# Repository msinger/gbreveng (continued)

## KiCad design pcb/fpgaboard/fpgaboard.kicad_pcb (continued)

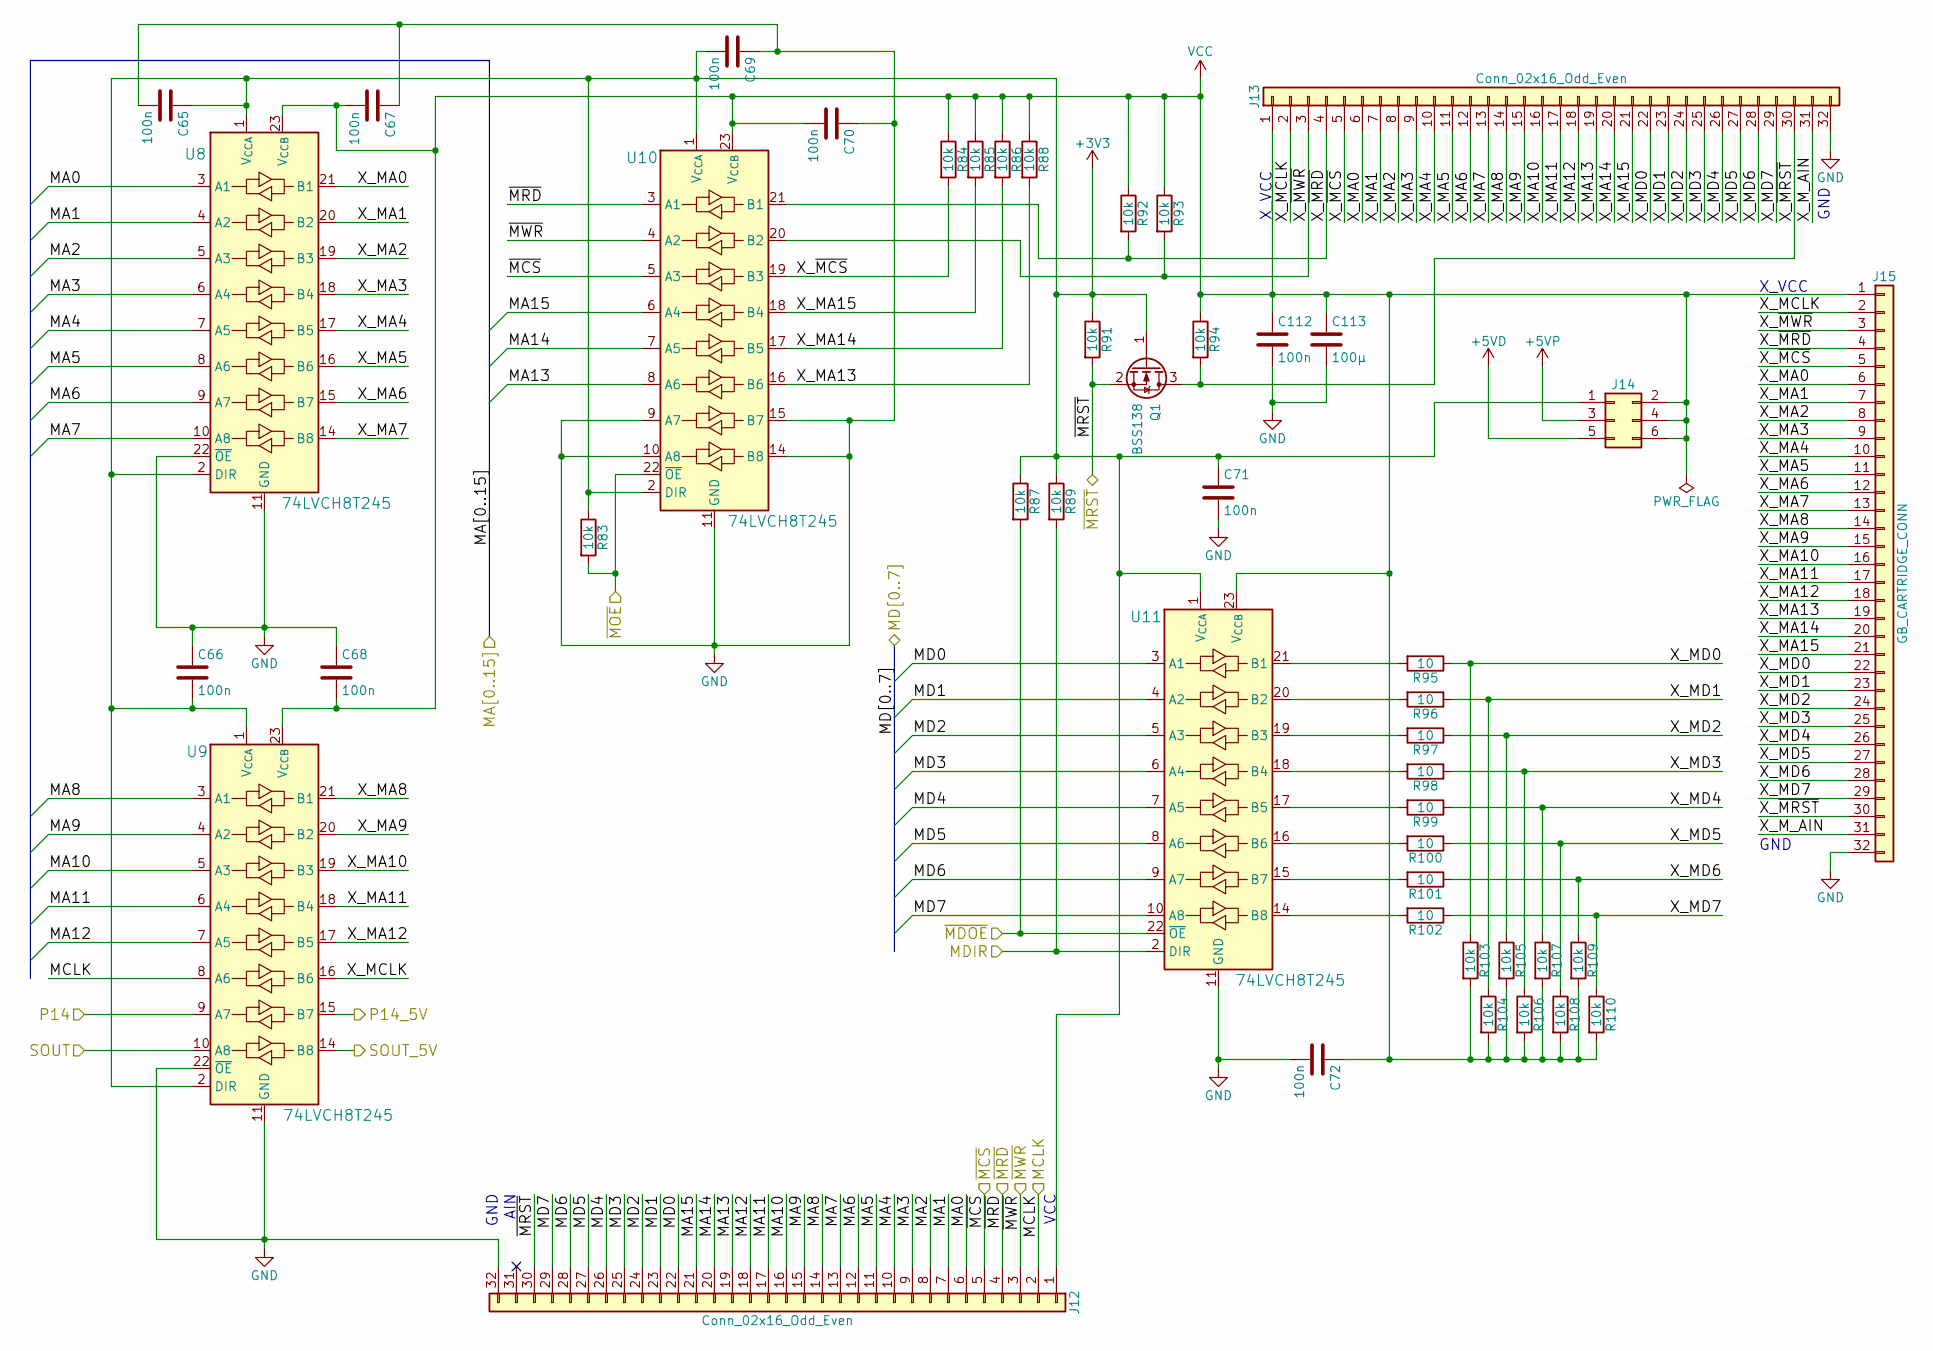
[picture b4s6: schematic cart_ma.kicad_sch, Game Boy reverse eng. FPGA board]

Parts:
C65, C66, C67, C68, C69, C70, C71, C72, C112: 100n; C_0402_1005Metric_Pad0.74x0.62mm_HandSolder
C113: 100µ; C_1206_3216Metric
J12, J13: Conn_02x16_Odd_Even; PinHeader_2x16_P2.54mm_Vertical
J14: Conn_02x03_Odd_Even; PinHeader_2x03_P2.54mm_Vertical
J15: GB_CARTRIDGE_CONN; Cartridge_Socket_SMD
Q1: BSS138; SOT-323_SC-70
R83, R84, R85, R86, R87, R88, R89, R91, R92, R93, R94, R103, R104, R105, R106, R107, R108, R109, R110: 10k; R_0402_1005Metric
R95, R96, R97, R98, R99, R100, R101, R102: 10; R_0603_1608Metric
U8, U9, U10, U11: 74LVCH8T245; TSSOP-24_4.4x7.8mm_P0.65mm

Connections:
+3V3: C65.1, C66.2, C69.2, C71.1, J12.1, J14.1, Q1.1 (G), R83.1, R87.1, R89.1, R91.1, U8.1 (V_{CCA}), U8.2 (DIR), U9.1 (V_{CCA}), U9.2 (DIR), U10.1 (V_{CCA}), U10.2 (DIR), U11.1 (V_{CCA}); also elsewhere on the board
+5VD: J14.5; also elsewhere on the board
+5VP: J14.3; also elsewhere on the board
/Bank0: Display, Keyboard, Clock/P14: U9.9 (A7); also elsewhere on the board
/Bank2: SDCard/CART_MA_CLK: J12.2, U9.8 (A6); also elsewhere on the board
/Bank2: SDCard/CART_MA_DIR: R89.2, U11.2 (DIR); also elsewhere on the board
/Bank2: SDCard/CART_MA_~CS: J12.5, U10.5 (A3); also elsewhere on the board
/Bank2: SDCard/CART_MA_~OE: R83.2, U10.22 (~OE); also elsewhere on the board
/Bank2: SDCard/CART_MA_~OE~_DATA: R87.2, U11.22 (~OE); also elsewhere on the board
/Bank2: SDCard/CART_MA_~RST: J12.30, Q1.2 (S), R91.2; also elsewhere on the board
/Bank2: SDCard/MA0: J12.6, U8.3 (A1); also elsewhere on the board
/Bank2: SDCard/MA1: J12.7, U8.4 (A2); also elsewhere on the board
/Bank2: SDCard/MA2: J12.8, U8.5 (A3); also elsewhere on the board
/Bank2: SDCard/MA3: J12.9, U8.6 (A4); also elsewhere on the board
/Bank2: SDCard/MA4: J12.10, U8.7 (A5); also elsewhere on the board
/Bank2: SDCard/MA5: J12.11, U8.8 (A6); also elsewhere on the board
/Bank2: SDCard/MA6: J12.12, U8.9 (A7); also elsewhere on the board
/Bank2: SDCard/MA7: J12.13, U8.10 (A8); also elsewhere on the board
/Bank2: SDCard/MA8: J12.14, U9.3 (A1); also elsewhere on the board
/Bank2: SDCard/MA9: J12.15, U9.4 (A2); also elsewhere on the board
/Bank2: SDCard/MA10: J12.16, U9.5 (A3); also elsewhere on the board
/Bank2: SDCard/MA11: J12.17, U9.6 (A4); also elsewhere on the board
/Bank2: SDCard/MA12: J12.18, U9.7 (A5); also elsewhere on the board
/Bank2: SDCard/MA13: J12.19, U10.8 (A6); also elsewhere on the board
/Bank2: SDCard/MA14: J12.20, U10.7 (A5); also elsewhere on the board
/Bank2: SDCard/MA15: J12.21, U10.6 (A4); also elsewhere on the board
/Bank2: SDCard/MD0: J12.22, U11.3 (A1); also elsewhere on the board
/Bank2: SDCard/MD1: J12.23, U11.4 (A2); also elsewhere on the board
/Bank2: SDCard/MD2: J12.24, U11.5 (A3); also elsewhere on the board
/Bank2: SDCard/MD3: J12.25, U11.6 (A4); also elsewhere on the board
/Bank2: SDCard/MD4: J12.26, U11.7 (A5); also elsewhere on the board
/Bank2: SDCard/MD5: J12.27, U11.8 (A6); also elsewhere on the board
/Bank2: SDCard/MD6: J12.28, U11.9 (A7); also elsewhere on the board
/Bank2: SDCard/MD7: J12.29, U11.10 (A8); also elsewhere on the board
/Bank3: LEDs, Switches/SOUT: U9.10 (A8); also elsewhere on the board
/Cartridge Master Slot/P14_5V: U9.15 (B7); also elsewhere on the board
/Cartridge Master Slot/SOUT_5V: U9.14 (B8); also elsewhere on the board
/Cartridge Master Slot/X_AIN: J13.31, J15.31
/Cartridge Master Slot/X_MA0: J13.6, J15.6, U8.21 (B1)
/Cartridge Master Slot/X_MA1: J13.7, J15.7, U8.20 (B2)
/Cartridge Master Slot/X_MA2: J13.8, J15.8, U8.19 (B3)
/Cartridge Master Slot/X_MA3: J13.9, J15.9, U8.18 (B4)
/Cartridge Master Slot/X_MA4: J13.10, J15.10, U8.17 (B5)
/Cartridge Master Slot/X_MA5: J13.11, J15.11, U8.16 (B6)
/Cartridge Master Slot/X_MA6: J13.12, J15.12, U8.15 (B7)
/Cartridge Master Slot/X_MA7: J13.13, J15.13, U8.14 (B8)
/Cartridge Master Slot/X_MA8: J13.14, J15.14, U9.21 (B1)
/Cartridge Master Slot/X_MA9: J13.15, J15.15, U9.20 (B2)
/Cartridge Master Slot/X_MA10: J13.16, J15.16, U9.19 (B3)
/Cartridge Master Slot/X_MA11: J13.17, J15.17, U9.18 (B4)
/Cartridge Master Slot/X_MA12: J13.18, J15.18, U9.17 (B5)
/Cartridge Master Slot/X_MA13: J13.19, J15.19, R88.2, U10.16 (B6)
/Cartridge Master Slot/X_MA14: J13.20, J15.20, R86.2, U10.17 (B5)
/Cartridge Master Slot/X_MA15: J13.21, J15.21, R85.2, U10.18 (B4)
/Cartridge Master Slot/X_MCLK: J13.2, J15.2, U9.16 (B6)
/Cartridge Master Slot/X_MD0: J13.22, J15.22, R95.1, R103.1
/Cartridge Master Slot/X_MD1: J13.23, J15.23, R96.1, R104.1
/Cartridge Master Slot/X_MD2: J13.24, J15.24, R97.1, R105.1
/Cartridge Master Slot/X_MD3: J13.25, J15.25, R98.1, R106.1
/Cartridge Master Slot/X_MD4: J13.26, J15.26, R99.1, R107.1
/Cartridge Master Slot/X_MD5: J13.27, J15.27, R100.1, R108.1
/Cartridge Master Slot/X_MD6: J13.28, J15.28, R101.1, R109.1
/Cartridge Master Slot/X_MD7: J13.29, J15.29, R102.1, R110.1
/Cartridge Master Slot/X_~MCS: J13.5, J15.5, R84.2, U10.19 (B3)
/Cartridge Master Slot/X_~MRD: J13.4, J15.4, R92.2, U10.21 (B1)
/Cartridge Master Slot/X_~MRST: J13.30, J15.30, Q1.3 (D), R94.2
/Cartridge Master Slot/X_~MWR: J13.3, J15.3, R93.2, U10.20 (B2)
/~MRD: J12.4, U10.3 (A1); also elsewhere on the board
/~MWR: J12.3, U10.4 (A2); also elsewhere on the board
GND: C65.2, C66.1, C67.2, C68.1, C69.1, C70.1, C71.2, C72.2, C112.2, C113.2, J12.32, J13.32, J15.32, U8.11 (GND), U8.12 (GND), U8.13 (GND), U8.22 (~OE), U9.11 (GND), U9.12 (GND), U9.13 (GND), U9.22 (~OE), U10.9 (A7), U10.10 (A8), U10.11 (GND), U10.12 (GND), U10.13 (GND), U10.14 (B8), U10.15 (B7), U11.11 (GND), U11.12 (GND), U11.13 (GND); also elsewhere on the board
unnamed: R95.2, U11.21 (B1)
unnamed: R96.2, U11.20 (B2)
unnamed: R97.2, U11.19 (B3)
unnamed: R98.2, U11.18 (B4)
unnamed: R99.2, U11.17 (B5)
unnamed: R100.2, U11.16 (B6)
unnamed: R101.2, U11.15 (B7)
unnamed: R102.2, U11.14 (B8)
VCC: C67.1, C68.2, C70.2, C72.1, C112.1, C113.1, J13.1, J14.2, J14.4, J14.6, J15.1, R84.1, R85.1, R86.1, R88.1, R92.1, R93.1, R94.1, R103.2, R104.2, R105.2, R106.2, R107.2, R108.2, R109.2, R110.2, U8.23 (V_{CCB}), U8.24 (V_{CCB}), U9.23 (V_{CCB}), U9.24 (V_{CCB}), U10.23 (V_{CCB}), U10.24 (V_{CCB}), U11.23 (V_{CCB}), U11.24 (V_{CCB}); also elsewhere on the board

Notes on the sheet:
X_VCC
VCC
AIN
GND

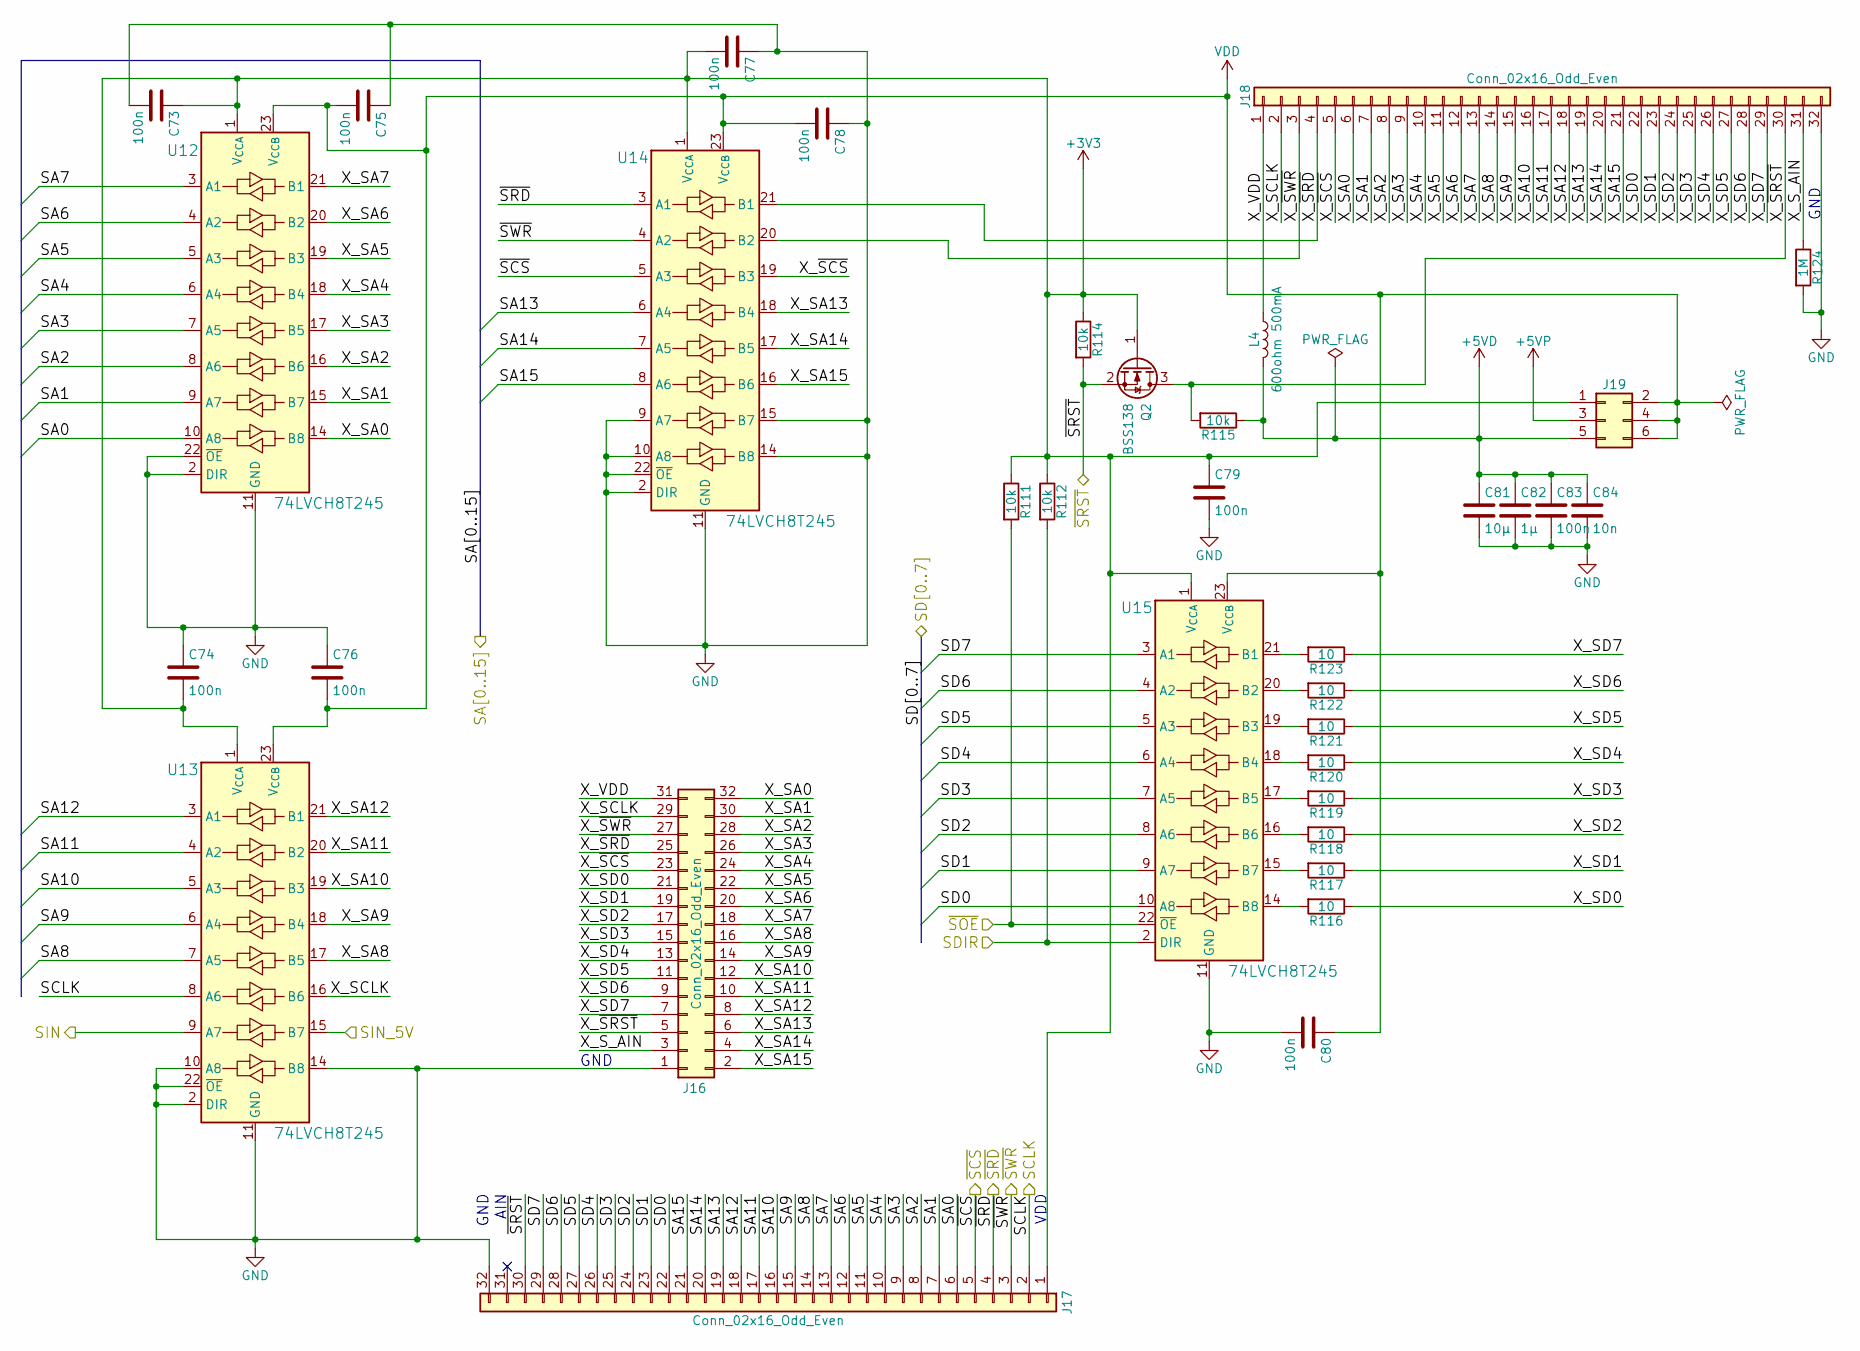
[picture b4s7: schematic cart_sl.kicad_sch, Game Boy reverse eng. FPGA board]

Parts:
C73, C74, C75, C76, C77, C78, C79, C80, C83: 100n; C_0402_1005Metric_Pad0.74x0.62mm_HandSolder
C81: 10µ; C_0603_1608Metric
C82: 1µ; C_0402_1005Metric_Pad0.74x0.62mm_HandSolder
C84: 10n; C_0402_1005Metric_Pad0.74x0.62mm_HandSolder
J16, J17, J18: Conn_02x16_Odd_Even; PinHeader_2x16_P2.54mm_Vertical
J19: Conn_02x03_Odd_Even; PinHeader_2x03_P2.54mm_Vertical
L4: 600ohm 500mA; L_0603_1608Metric
Q2: BSS138; SOT-323_SC-70
R111, R112, R114, R115: 10k; R_0402_1005Metric
R116, R117, R118, R119, R120, R121, R122, R123: 10; R_0603_1608Metric
R124: 1M; R_0402_1005Metric
U12, U13, U14, U15: 74LVCH8T245; TSSOP-24_4.4x7.8mm_P0.65mm

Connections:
+3V3: C73.1, C74.2, C77.2, C79.1, J17.1, J19.1, Q2.1 (G), R111.1, R112.1, R114.1, U12.1 (V_{CCA}), U13.1 (V_{CCA}), U14.1 (V_{CCA}), U15.1 (V_{CCA}); also elsewhere on the board
+5VD: C81.1, C82.1, C83.1, C84.1, J19.5, L4.2, R115.1; also elsewhere on the board
+5VP: J19.3; also elsewhere on the board
/Bank0: Display, Keyboard, Clock/A0: J17.6, U12.10 (A8); also elsewhere on the board
/Bank0: Display, Keyboard, Clock/A1: J17.7, U12.9 (A7); also elsewhere on the board
/Bank0: Display, Keyboard, Clock/A2: J17.8, U12.8 (A6); also elsewhere on the board
/Bank0: Display, Keyboard, Clock/A3: J17.9, U12.7 (A5); also elsewhere on the board
/Bank0: Display, Keyboard, Clock/A4: J17.10, U12.6 (A4); also elsewhere on the board
/Bank0: Display, Keyboard, Clock/A5: J17.11, U12.5 (A3); also elsewhere on the board
/Bank0: Display, Keyboard, Clock/A6: J17.12, U12.4 (A2); also elsewhere on the board
/Bank0: Display, Keyboard, Clock/A7: J17.13, U12.3 (A1); also elsewhere on the board
/Bank0: Display, Keyboard, Clock/A8: J17.14, U13.7 (A5); also elsewhere on the board
/Bank0: Display, Keyboard, Clock/A9: J17.15, U13.6 (A4); also elsewhere on the board
/Bank0: Display, Keyboard, Clock/A10: J17.16, U13.5 (A3); also elsewhere on the board
/Bank0: Display, Keyboard, Clock/A11: J17.17, U13.4 (A2); also elsewhere on the board
/Bank0: Display, Keyboard, Clock/A12: J17.18, U13.3 (A1); also elsewhere on the board
/Bank0: Display, Keyboard, Clock/A13: J17.19, U14.6 (A4); also elsewhere on the board
/Bank0: Display, Keyboard, Clock/A14: J17.20, U14.7 (A5); also elsewhere on the board
/Bank0: Display, Keyboard, Clock/A15: J17.21, U14.8 (A6); also elsewhere on the board
/Bank0: Display, Keyboard, Clock/CART_SL_CLK: J17.2, U13.8 (A6); also elsewhere on the board
/Bank0: Display, Keyboard, Clock/CART_SL_~RD: J17.4, U14.3 (A1); also elsewhere on the board
/Bank0: Display, Keyboard, Clock/CART_SL_~WR: J17.3, U14.4 (A2); also elsewhere on the board
/Bank1: GPIOA/CART_SL_DIR: R112.2, U15.2 (DIR); also elsewhere on the board
/Bank1: GPIOA/CART_SL_~CS: J17.5, U14.5 (A3); also elsewhere on the board
/Bank1: GPIOA/CART_SL_~OE: R111.2, U15.22 (~OE); also elsewhere on the board
/Bank1: GPIOA/CART_SL_~RST: J17.30, Q2.2 (S), R114.2; also elsewhere on the board
/Bank1: GPIOA/D0: J17.22, U15.10 (A8); also elsewhere on the board
/Bank1: GPIOA/D1: J17.23, U15.9 (A7); also elsewhere on the board
/Bank1: GPIOA/D2: J17.24, U15.8 (A6); also elsewhere on the board
/Bank1: GPIOA/D3: J17.25, U15.7 (A5); also elsewhere on the board
/Bank1: GPIOA/D4: J17.26, U15.6 (A4); also elsewhere on the board
/Bank1: GPIOA/D5: J17.27, U15.5 (A3); also elsewhere on the board
/Bank1: GPIOA/D6: J17.28, U15.4 (A2); also elsewhere on the board
/Bank1: GPIOA/D7: J17.29, U15.3 (A1); also elsewhere on the board
/Cartridge Slave Slot/X_A0: J16.32, J18.6, U12.14 (B8)
/Cartridge Slave Slot/X_A1: J16.30, J18.7, U12.15 (B7)
/Cartridge Slave Slot/X_A2: J16.28, J18.8, U12.16 (B6)
/Cartridge Slave Slot/X_A3: J16.26, J18.9, U12.17 (B5)
/Cartridge Slave Slot/X_A4: J16.24, J18.10, U12.18 (B4)
/Cartridge Slave Slot/X_A5: J16.22, J18.11, U12.19 (B3)
/Cartridge Slave Slot/X_A6: J16.20, J18.12, U12.20 (B2)
/Cartridge Slave Slot/X_A7: J16.18, J18.13, U12.21 (B1)
/Cartridge Slave Slot/X_A8: J16.16, J18.14, U13.17 (B5)
/Cartridge Slave Slot/X_A9: J16.14, J18.15, U13.18 (B4)
/Cartridge Slave Slot/X_A10: J16.12, J18.16, U13.19 (B3)
/Cartridge Slave Slot/X_A11: J16.10, J18.17, U13.20 (B2)
/Cartridge Slave Slot/X_A12: J16.8, J18.18, U13.21 (B1)
/Cartridge Slave Slot/X_A13: J16.6, J18.19, U14.18 (B4)
/Cartridge Slave Slot/X_A14: J16.4, J18.20, U14.17 (B5)
/Cartridge Slave Slot/X_A15: J16.2, J18.21, U14.16 (B6)
/Cartridge Slave Slot/X_AIN: J16.3, J18.31, R124.1
/Cartridge Slave Slot/X_CLK: J16.29, J18.2, U13.16 (B6)
/Cartridge Slave Slot/X_D0: J16.21, J18.22, R116.1
/Cartridge Slave Slot/X_D1: J16.19, J18.23, R117.1
/Cartridge Slave Slot/X_D2: J16.17, J18.24, R118.1
/Cartridge Slave Slot/X_D3: J16.15, J18.25, R119.1
/Cartridge Slave Slot/X_D4: J16.13, J18.26, R120.1
/Cartridge Slave Slot/X_D5: J16.11, J18.27, R121.1
/Cartridge Slave Slot/X_D6: J16.9, J18.28, R122.1
/Cartridge Slave Slot/X_D7: J16.7, J18.29, R123.1
/Cartridge Slave Slot/X_VDD: J16.31, J18.1, L4.1
/Cartridge Slave Slot/X_~CS: J16.23, J18.5, U14.19 (B3)
/Cartridge Slave Slot/X_~RD: J16.25, J18.4, U14.21 (B1)
/Cartridge Slave Slot/X_~RST: J16.5, J18.30, Q2.3 (D), R115.2
/Cartridge Slave Slot/X_~WR: J16.27, J18.3, U14.20 (B2)
/SIN: U13.9 (A7); also elsewhere on the board
/SIN_5V: U13.15 (B7); also elsewhere on the board
GND: C73.2, C74.1, C75.2, C76.1, C77.1, C78.1, C79.2, C80.2, C81.2, C82.2, C83.2, C84.2, J16.1, J17.32, J18.32, R124.2, U12.2 (DIR), U12.11 (GND), U12.12 (GND), U12.13 (GND), U12.22 (~OE), U13.2 (DIR), U13.10 (A8), U13.11 (GND), U13.12 (GND), U13.13 (GND), U13.14 (B8), U13.22 (~OE), U14.2 (DIR), U14.9 (A7), U14.10 (A8), U14.11 (GND), U14.12 (GND), U14.13 (GND), U14.14 (B8), U14.15 (B7), U14.22 (~OE), U15.11 (GND), U15.12 (GND), U15.13 (GND); also elsewhere on the board
unnamed: R116.2, U15.14 (B8)
unnamed: R117.2, U15.15 (B7)
unnamed: R118.2, U15.16 (B6)
unnamed: R119.2, U15.17 (B5)
unnamed: R120.2, U15.18 (B4)
unnamed: R121.2, U15.19 (B3)
unnamed: R122.2, U15.20 (B2)
unnamed: R123.2, U15.21 (B1)
VDD: C75.1, C76.2, C78.2, C80.1, J19.2, J19.4, J19.6, U12.23 (V_{CCB}), U12.24 (V_{CCB}), U13.23 (V_{CCB}), U13.24 (V_{CCB}), U14.23 (V_{CCB}), U14.24 (V_{CCB}), U15.23 (V_{CCB}), U15.24 (V_{CCB}); also elsewhere on the board

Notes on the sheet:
GND
AIN
VDD

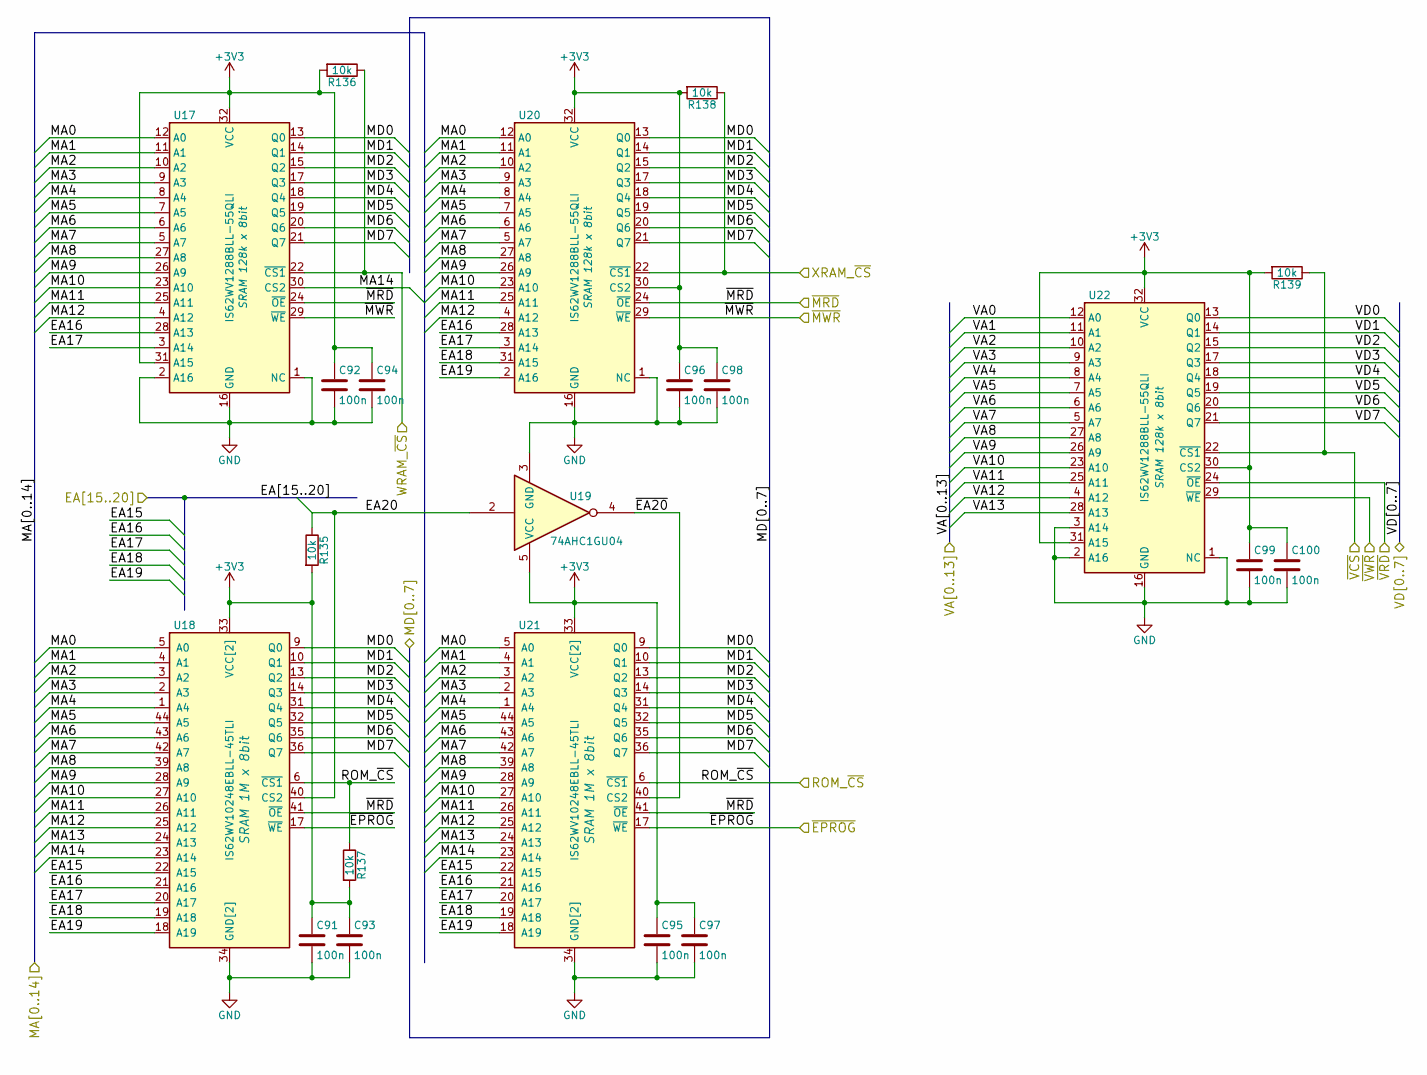
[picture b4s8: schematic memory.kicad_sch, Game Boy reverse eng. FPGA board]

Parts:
C91, C92, C93, C94, C95, C96, C97, C98, C99, C100: 100n; C_0402_1005Metric_Pad0.74x0.62mm_HandSolder
R135, R136, R137, R138, R139: 10k; R_0402_1005Metric
U17, U20, U22: IS62WV1288BLL-55QLI; SSOP-32_11.305x20.495mm_P1.27mm
U18, U21: IS62WV10248EBLL-45TLI; TSOP-II-44_10.16x18.41mm_P0.8mm
U19: 74AHC1GU04; SOT-353_SC-70-5

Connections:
+3V3: C91.1, C92.1, C93.1, C94.1, C95.1, C96.1, C97.1, C98.1, C99.1, C100.1, R135.2, R136.2, R137.2, R138.2, R139.2, U17.31 (A15), U17.32 (VCC), U18.11 (VCC[2]), U18.33 (VCC[2]), U19.5 (VCC), U20.30 (CS2), U20.32 (VCC), U21.11 (VCC[2]), U21.33 (VCC[2]), U22.30 (CS2), U22.31 (A15), U22.32 (VCC); also elsewhere on the board
/Bank1: GPIOA/VA0: U22.12 (A0); also elsewhere on the board
/Bank1: GPIOA/VA1: U22.11 (A1); also elsewhere on the board
/Bank1: GPIOA/VA2: U22.10 (A2); also elsewhere on the board
/Bank1: GPIOA/VA3: U22.9 (A3); also elsewhere on the board
/Bank1: GPIOA/VA4: U22.8 (A4); also elsewhere on the board
/Bank1: GPIOA/VA5: U22.7 (A5); also elsewhere on the board
/Bank1: GPIOA/VA6: U22.6 (A6); also elsewhere on the board
/Bank1: GPIOA/VA7: U22.5 (A7); also elsewhere on the board
/Bank1: GPIOA/VA8: U22.27 (A8); also elsewhere on the board
/Bank1: GPIOA/VA9: U22.26 (A9); also elsewhere on the board
/Bank1: GPIOA/VA10: U22.23 (A10); also elsewhere on the board
/Bank1: GPIOA/VA11: U22.25 (A11); also elsewhere on the board
/Bank1: GPIOA/VA12: U22.4 (A12); also elsewhere on the board
/Bank1: GPIOA/VA13: U22.28 (A13); also elsewhere on the board
/Bank1: GPIOA/VD0: U22.13 (Q0); also elsewhere on the board
/Bank1: GPIOA/VD1: U22.14 (Q1); also elsewhere on the board
/Bank1: GPIOA/VD2: U22.15 (Q2); also elsewhere on the board
/Bank1: GPIOA/VD3: U22.17 (Q3); also elsewhere on the board
/Bank1: GPIOA/VD4: U22.18 (Q4); also elsewhere on the board
/Bank1: GPIOA/VD5: U22.19 (Q5); also elsewhere on the board
/Bank1: GPIOA/VD6: U22.20 (Q6); also elsewhere on the board
/Bank1: GPIOA/VD7: U22.21 (Q7); also elsewhere on the board
/Bank2: SDCard/EA15: U18.22 (A15), U21.22 (A15); also elsewhere on the board
/Bank2: SDCard/EA16: U17.28 (A13), U18.21 (A16), U20.28 (A13), U21.21 (A16); also elsewhere on the board
/Bank2: SDCard/EA17: U17.3 (A14), U18.20 (A17), U20.3 (A14), U21.20 (A17); also elsewhere on the board
/Bank2: SDCard/EA18: U18.19 (A18), U20.31 (A15), U21.19 (A18); also elsewhere on the board
/Bank2: SDCard/EA19: U18.18 (A19), U20.2 (A16), U21.18 (A19); also elsewhere on the board
/Bank2: SDCard/EA20: R135.1, U18.40 (CS2), U19.2; also elsewhere on the board
/Bank2: SDCard/MA0: U17.12 (A0), U18.5 (A0), U20.12 (A0), U21.5 (A0); also elsewhere on the board
/Bank2: SDCard/MA1: U17.11 (A1), U18.4 (A1), U20.11 (A1), U21.4 (A1); also elsewhere on the board
/Bank2: SDCard/MA2: U17.10 (A2), U18.3 (A2), U20.10 (A2), U21.3 (A2); also elsewhere on the board
/Bank2: SDCard/MA3: U17.9 (A3), U18.2 (A3), U20.9 (A3), U21.2 (A3); also elsewhere on the board
/Bank2: SDCard/MA4: U17.8 (A4), U18.1 (A4), U20.8 (A4), U21.1 (A4); also elsewhere on the board
/Bank2: SDCard/MA5: U17.7 (A5), U18.44 (A5), U20.7 (A5), U21.44 (A5); also elsewhere on the board
/Bank2: SDCard/MA6: U17.6 (A6), U18.43 (A6), U20.6 (A6), U21.43 (A6); also elsewhere on the board
/Bank2: SDCard/MA7: U17.5 (A7), U18.42 (A7), U20.5 (A7), U21.42 (A7); also elsewhere on the board
/Bank2: SDCard/MA8: U17.27 (A8), U18.39 (A8), U20.27 (A8), U21.39 (A8); also elsewhere on the board
/Bank2: SDCard/MA9: U17.26 (A9), U18.28 (A9), U20.26 (A9), U21.28 (A9); also elsewhere on the board
/Bank2: SDCard/MA10: U17.23 (A10), U18.27 (A10), U20.23 (A10), U21.27 (A10); also elsewhere on the board
/Bank2: SDCard/MA11: U17.25 (A11), U18.26 (A11), U20.25 (A11), U21.26 (A11); also elsewhere on the board
/Bank2: SDCard/MA12: U17.4 (A12), U18.25 (A12), U20.4 (A12), U21.25 (A12); also elsewhere on the board
/Bank2: SDCard/MA13: U18.24 (A13), U21.24 (A13); also elsewhere on the board
/Bank2: SDCard/MA14: U17.30 (CS2), U18.23 (A14), U21.23 (A14); also elsewhere on the board
/Bank2: SDCard/MD0: U17.13 (Q0), U18.9 (Q0), U20.13 (Q0), U21.9 (Q0); also elsewhere on the board
/Bank2: SDCard/MD1: U17.14 (Q1), U18.10 (Q1), U20.14 (Q1), U21.10 (Q1); also elsewhere on the board
/Bank2: SDCard/MD2: U17.15 (Q2), U18.13 (Q2), U20.15 (Q2), U21.13 (Q2); also elsewhere on the board
/Bank2: SDCard/MD3: U17.17 (Q3), U18.14 (Q3), U20.17 (Q3), U21.14 (Q3); also elsewhere on the board
/Bank2: SDCard/MD4: U17.18 (Q4), U18.31 (Q4), U20.18 (Q4), U21.31 (Q4); also elsewhere on the board
/Bank2: SDCard/MD5: U17.19 (Q5), U18.32 (Q5), U20.19 (Q5), U21.32 (Q5); also elsewhere on the board
/Bank2: SDCard/MD6: U17.20 (Q6), U18.35 (Q6), U20.20 (Q6), U21.35 (Q6); also elsewhere on the board
/Bank2: SDCard/MD7: U17.21 (Q7), U18.36 (Q7), U20.21 (Q7), U21.36 (Q7); also elsewhere on the board
/Bank2: SDCard/ONBRD_~PROG: U18.17 (~WE), U21.17 (~WE); also elsewhere on the board
/Bank2: SDCard/ROM_~CS: R137.1, U18.6 (~CS1), U21.6 (~CS1); also elsewhere on the board
/Bank2: SDCard/WRAM_~CS: R136.1, U17.22 (~CS1); also elsewhere on the board
/Bank2: SDCard/XRAM_~CS: R138.1, U20.22 (~CS1); also elsewhere on the board
/Memory/~MA20: U19.4, U21.40 (CS2)
/~MRD: U17.24 (~OE), U18.41 (~OE), U20.24 (~OE), U21.41 (~OE); also elsewhere on the board
/~MWR: U17.29 (~WE), U20.29 (~WE); also elsewhere on the board
/~VCS: R139.1, U22.22 (~CS1); also elsewhere on the board
/~VRD: U22.24 (~OE); also elsewhere on the board
/~VWR: U22.29 (~WE); also elsewhere on the board
GND: C91.2, C92.2, C93.2, C94.2, C95.2, C96.2, C97.2, C98.2, C99.2, C100.2, U17.1 (NC), U17.2 (A16), U17.16 (GND), U18.12 (GND[2]), U18.34 (GND[2]), U19.3 (GND), U20.1 (NC), U20.16 (GND), U21.12 (GND[2]), U21.34 (GND[2]), U22.1 (NC), U22.2 (A16), U22.3 (A14), U22.16 (GND); also elsewhere on the board

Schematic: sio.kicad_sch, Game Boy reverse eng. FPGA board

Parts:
C85, C86: 100n; C_0402_1005Metric_Pad0.74x0.62mm_HandSolder
C87, C88, C89, C90: 100p; C_0402_1005Metric_Pad0.74x0.62mm_HandSolder
D19, D20, D21, D22: BAV199WQ; SOT-323_SC-70
D23: BAV100; D_MiniMELF
J20, J22: Conn_02x05_Odd_Even; PinHeader_2x05_P2.54mm_Vertical
J21, J23, J24: Conn_02x03_Odd_Even; PinHeader_2x03_P2.54mm_Vertical
J25: CGB_ELP; CGB_External-Link-Port
R125, R126, R128, R129: 10k; R_0402_1005Metric
R130, R131, R132, R133: 220; R_0805_2012Metric
U16: 74LVCH8T245; TSSOP-24_4.4x7.8mm_P0.65mm

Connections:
+3V3: C85.1, J20.2, J21.1, J23.1, R125.1, R126.1, U16.1 (V_{CCA}); also elsewhere on the board
+5VD: J23.5; also elsewhere on the board
+5VP: J23.3; also elsewhere on the board
/Bank0: Display, Keyboard, Clock/P14: J21.4; also elsewhere on the board
/Bank3: LEDs, Switches/GPIO_B1: J20.4, U16.4 (A2); also elsewhere on the board
/Bank3: LEDs, Switches/GPIO_B2: J20.5, U16.5 (A3); also elsewhere on the board
/Bank3: LEDs, Switches/GPIO_B3: J20.6, U16.6 (A4); also elsewhere on the board
/Bank3: LEDs, Switches/GPIO_B4: J20.7, U16.7 (A5); also elsewhere on the board
/Bank3: LEDs, Switches/GPIO_B5: J20.8, U16.8 (A6); also elsewhere on the board
/Bank3: LEDs, Switches/GPIO_B_~OE: R126.2, U16.22 (~OE); also elsewhere on the board
/Bank3: LEDs, Switches/SCX: J20.3, J21.5, U16.3 (A1); also elsewhere on the board
/Bank3: LEDs, Switches/SOUT: J21.2; also elsewhere on the board
/Cartridge Master Slot/P14_5V: R133.2; also elsewhere on the board
/Cartridge Master Slot/SOUT_5V: R132.2; also elsewhere on the board
/External Link Port, GPIOB/DIR: R125.2, U16.2 (DIR); also elsewhere on the board
/External Link Port, GPIOB/ELP_P14: C88.1, D20.3 (common), J24.4, J25.4, R133.1
/External Link Port, GPIOB/ELP_SCX: C87.1, D19.3 (common), J24.5, J25.5, R131.1
/External Link Port, GPIOB/ELP_SIN: C89.1, D21.3 (common), J24.3, J25.3, R130.1
/External Link Port, GPIOB/ELP_SOUT: C90.1, D22.3 (common), J24.2, J25.2, R132.1
/External Link Port, GPIOB/VCC_ELP: D23.1 (K), J24.1, J25.1
/External Link Port, GPIOB/VCC_GPIO_B: C86.1, D19.2 (K), D23.2 (A), J22.2, J23.2, J23.4, J23.6, R128.1, R129.1, U16.23 (V_{CCB}), U16.24 (V_{CCB})
/External Link Port, GPIOB/XGPIO_B0: J22.3, R128.2, R131.2, U16.21 (B1)
/External Link Port, GPIOB/XGPIO_B1: J22.4, U16.20 (B2)
/External Link Port, GPIOB/XGPIO_B2: J22.5, U16.19 (B3)
/External Link Port, GPIOB/XGPIO_B3: J22.6, U16.18 (B4)
/External Link Port, GPIOB/XGPIO_B4: J22.7, U16.17 (B5)
/External Link Port, GPIOB/XGPIO_B5: J22.8, U16.16 (B6)
/External Link Port, GPIOB/XGPIO_B6: J22.9, U16.15 (B7)
/External Link Port, GPIOB/XGPIO_B7: J22.10, U16.14 (B8)
/GPIO_B6: J20.9, U16.9 (A7); also elsewhere on the board
/GPIO_B7: J20.10, U16.10 (A8); also elsewhere on the board
/SIN: J21.3; also elsewhere on the board
/SIN_5V: R129.2, R130.2; also elsewhere on the board
GND: C85.2, C86.2, C87.2, C88.2, C89.2, C90.2, D19.1 (A), D20.1 (A), D21.1 (A), D22.1 (A), J20.1, J21.6, J22.1, J24.6, J25.6, J25.7, U16.11 (GND), U16.12 (GND), U16.13 (GND); also elsewhere on the board
VCC: D20.2 (K), D22.2 (K); also elsewhere on the board
VDD: D21.2 (K); also elsewhere on the board

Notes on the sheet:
SHLD
SOUT
SIN
P14
GND
VCC
SCX
GPIO_B0

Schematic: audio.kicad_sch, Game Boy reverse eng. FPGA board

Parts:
C101, C102, C103: 1µ; C_0402_1005Metric_Pad0.74x0.62mm_HandSolder
C104, C105: 100n; C_0402_1005Metric_Pad0.74x0.62mm_HandSolder
C106, C107, C108: 47n; C_0402_1005Metric_Pad0.74x0.62mm_HandSolder
C109, C110: 100µ; C_1206_3216Metric
J26: Conn_02x05_Odd_Even; PinHeader_2x05_P2.54mm_Vertical
J27: Conn_02x03_Odd_Even; PinHeader_2x03_P2.54mm_Vertical
J28: SJ1-3533NG; Jack_3.5mm_CUI_SJ1-3533NG_Horizontal
JP2: Jumper_2_Bridged; PinHeader_1x02_P2.54mm_Vertical
L5, L6: 33n; L_0402_1005Metric
LS1: 8ohm; PinHeader_1x02_P2.54mm_Vertical
R140, R141, R142: 47; R_0402_1005Metric
RV1, RV2, RV3: 1k; Potentiometer_Vishay_TS53YL_Vertical
U23, U24: TDA7050; DIP-8_W7.62mm_Socket

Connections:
+3V3: J26.3, J26.4, J27.1; also elsewhere on the board
+5VD: J27.5; also elsewhere on the board
+5VP: J27.3; also elsewhere on the board
/Audio/PWM_L: C102.1, J26.7; also elsewhere on the board
/Audio/PWM_M: C103.1, J26.6; also elsewhere on the board
/Audio/PWM_R: C101.1, J26.8; also elsewhere on the board
/Audio/SPEAKER: C108.1, JP2.2 (B); also elsewhere on the board
/Audio/VCC_AMP: C104.2, C105.2, J26.1, J26.2, J27.2, J27.4, J27.6, U23.8 (V+), U24.8 (V+)
GND: C104.1, C105.1, C106.2, C107.2, C108.2, J26.9, J26.10, J28.S, RV1.3, RV2.3, RV3.3, U23.2 (-), U23.4 (+), U23.5 (GND), U24.1 (+), U24.4 (+), U24.5 (GND); also elsewhere on the board
unnamed: C101.2, R140.1
unnamed: C102.2, R141.1
unnamed: C103.2, R142.1
unnamed: C106.1, L5.2, U24.7
unnamed: C107.1, L6.2, U24.6
unnamed: C109.1, J28.T
unnamed: C109.2, L5.1
unnamed: C110.1, J28.R
unnamed: C110.2, L6.1
unnamed: JP2.1 (A), LS1.1, U23.7
unnamed: LS1.2, U23.6
unnamed: R140.2, RV1.1
unnamed: R141.2, RV2.1
unnamed: R142.2, RV3.1
unnamed: RV1.2, U24.3 (-)
unnamed: RV2.2, U24.2 (-)
unnamed: RV3.2, U23.1 (+), U23.3 (-)
